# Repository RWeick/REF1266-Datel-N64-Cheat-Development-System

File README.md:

# REF1266-Datel-N64-Cheat-Development-System
Everything necessary to produce the Datel N64 Cheat Development System

This device is explained in some detail [here](https://www.nesworld.com/n64-dateltrainercart.php).

Brought back from the edge of extinction, this is the predecessor to the N64 Gameshark Pro's Code Generator. This device is used to hack codes for the N64 in concert with the [Datel PC Comms ISA Card](https://github.com/RWeick/REF1190-Datel-PC-Comms-Link-ISA-Card). The firmwares listed show the compatible games it can hack codes for. I have not yet tested if they are compatible with other games as well. The firmware can be flashed to the device by writing it directly to the eeproms prior to soldering them down or via the Sanni Cartridge Reader's Flash Gameshark function. Once a firmware is written, the firmwares can be swapped using the Sharklink software in the PC Comms Link repository.

As I have not ever seen one of these myself in person, the dimensions of the PCB may be slightly off from the original. However, the schematic and pcb trace connections are 100% the same as the original as verified by testing the device. This was possible due to the extensive reverse engineering I've already done on the N64 Gameshark. All necessary parts can be harvested from any N64 Gameshark or Gameshark Pro, with the exception of the parallel port which is a horizontal mounted male port. Happy making.

PCB Thickness: 1.2 mm

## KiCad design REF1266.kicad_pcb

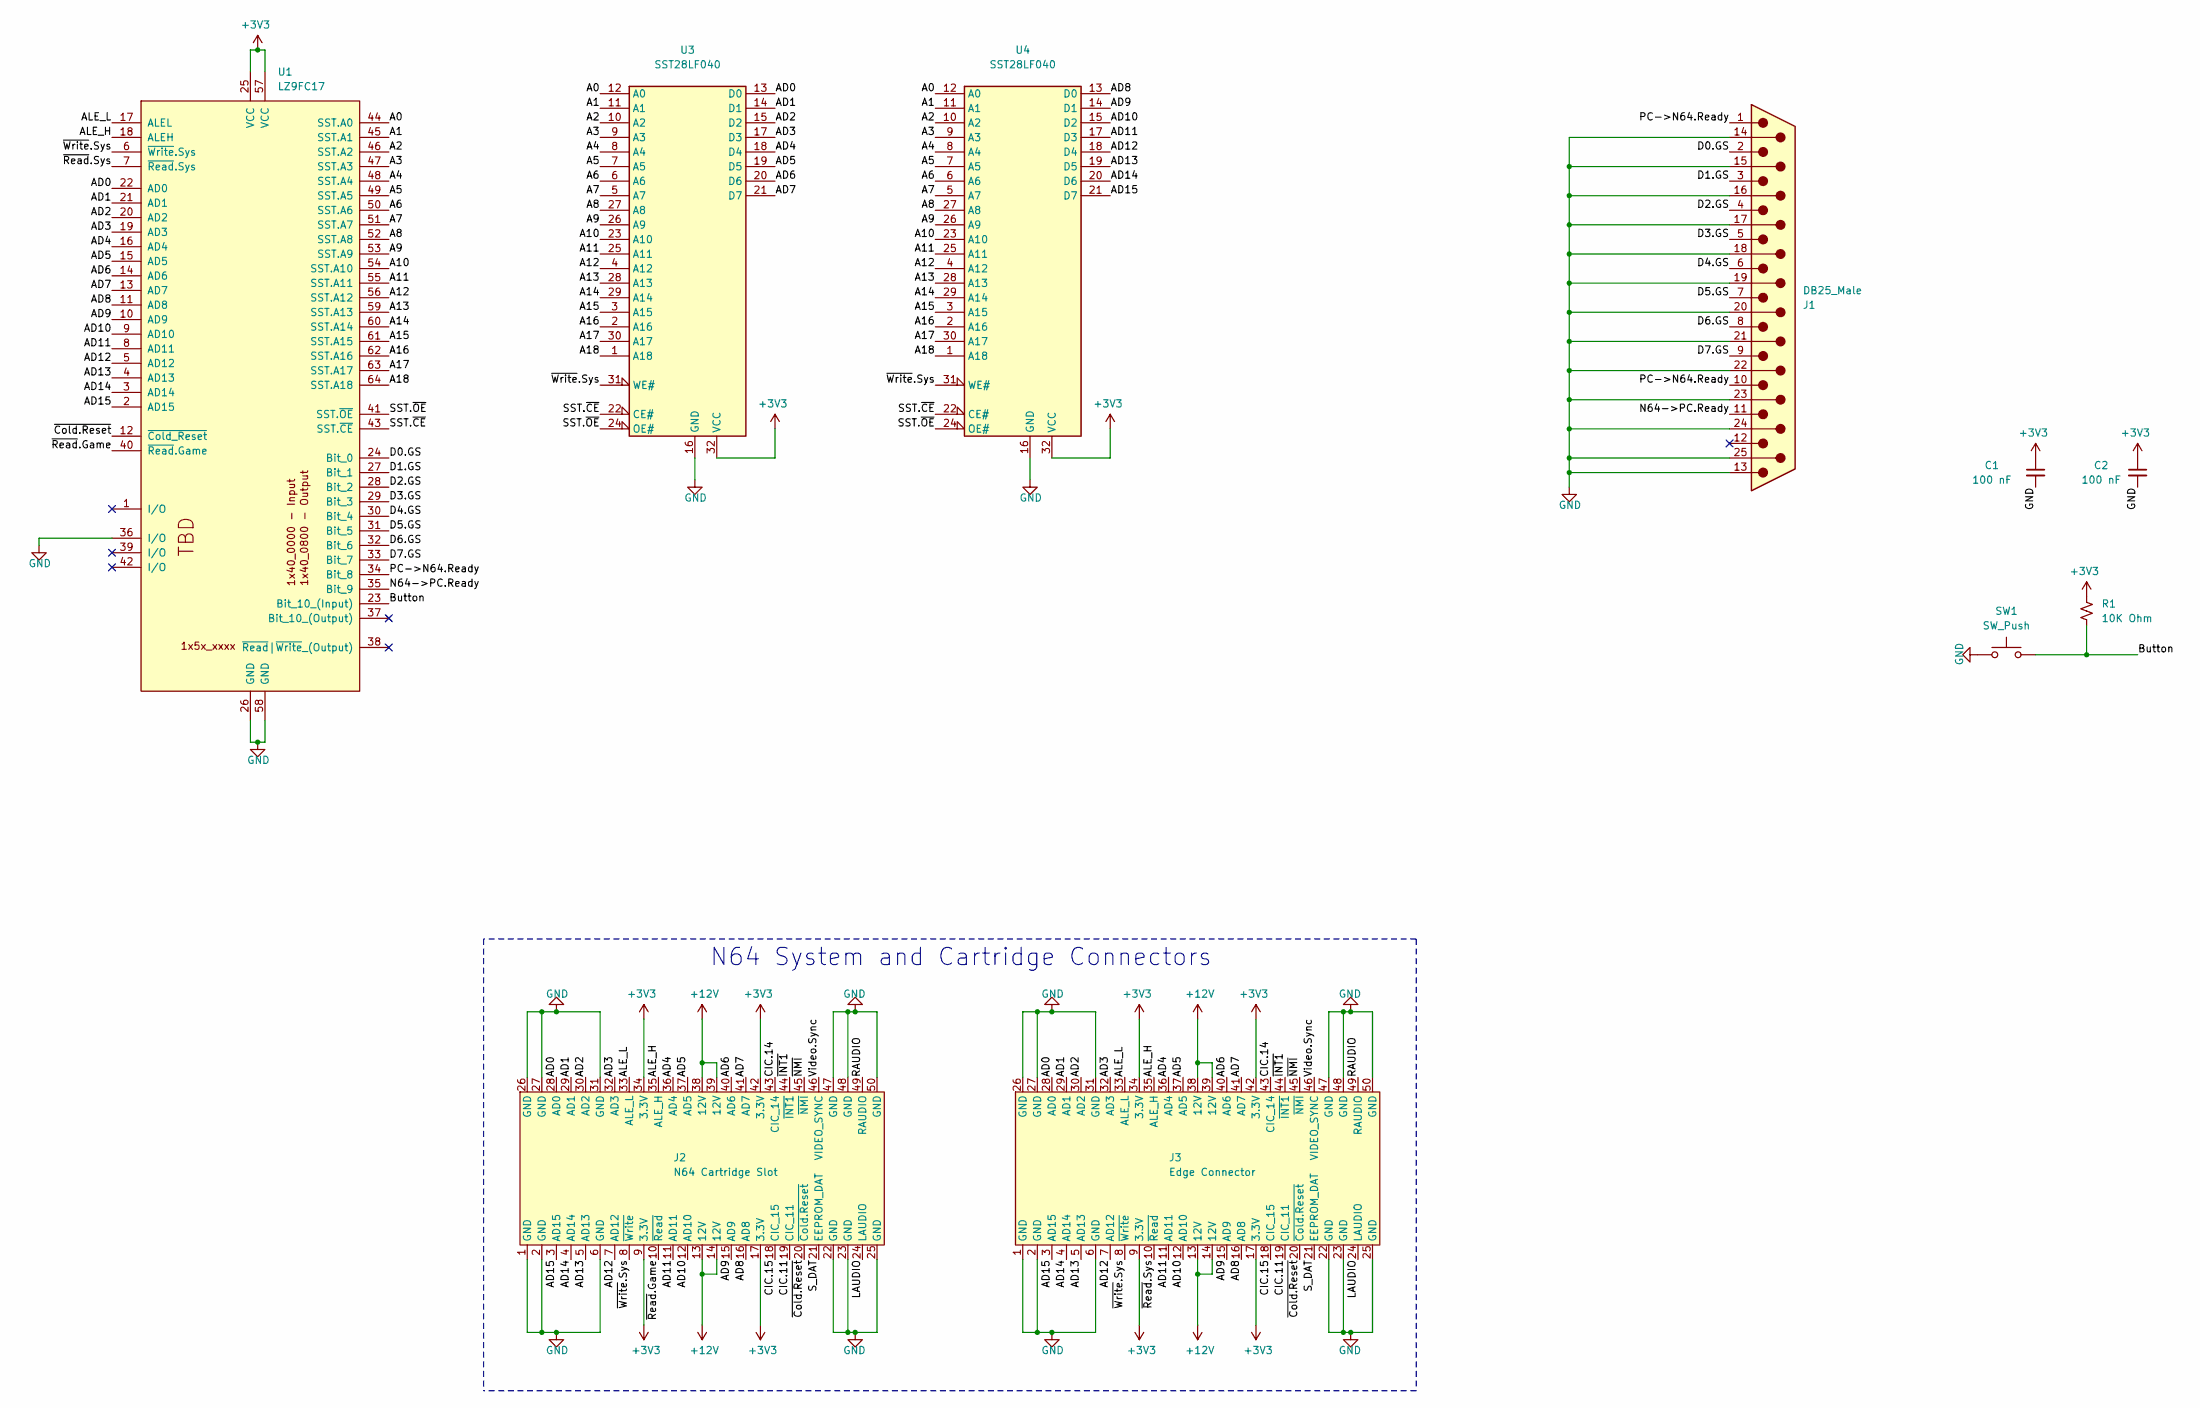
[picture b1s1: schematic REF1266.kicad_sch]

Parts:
C1, C2: 100 nF; 100 nF Cap
J1: DB25_Male; DSUB-25_Socket_Vertical_P2.77x2.84mm_MountingHoles
J2: N64 Cartridge Slot; Cartridge Slot
J3: Edge Connector; Bottom Edge Connector
R1: 10K Ohm; 10k Ohm Resistor
SW1: SW_Push; 6mm Push Button
U1: LZ9FC17; LZ9FC17 GAL
U3, U4: SST28LF040; PLCC32

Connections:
+3V3: C1.1, C2.1, J2.9 (3.3V), J2.17 (3.3V), J2.34 (3.3V), J2.42 (3.3V), J3.9 (3.3V), J3.17 (3.3V), J3.34 (3.3V), J3.42 (3.3V), R1.2, U1.25 (VCC), U1.57 (VCC), U3.32 (VCC), U4.32 (VCC)
+12V: J2.13 (12V), J2.14 (12V), J2.38 (12V), J2.39 (12V), J3.13 (12V), J3.14 (12V), J3.38 (12V), J3.39 (12V)
/A0: U1.44 (SST.A0), U3.12 (A0), U4.12 (A0)
/A1: U1.45 (SST.A1), U3.11 (A1), U4.11 (A1)
/A2: U1.46 (SST.A2), U3.10 (A2), U4.10 (A2)
/A3: U1.47 (SST.A3), U3.9 (A3), U4.9 (A3)
/A4: U1.48 (SST.A4), U3.8 (A4), U4.8 (A4)
/A5: U1.49 (SST.A5), U3.7 (A5), U4.7 (A5)
/A6: U1.50 (SST.A6), U3.6 (A6), U4.6 (A6)
/A7: U1.51 (SST.A7), U3.5 (A7), U4.5 (A7)
/A8: U1.52 (SST.A8), U3.27 (A8), U4.27 (A8)
/A9: U1.53 (SST.A9), U3.26 (A9), U4.26 (A9)
/A10: U1.54 (SST.A10), U3.23 (A10), U4.23 (A10)
/A11: U1.55 (SST.A11), U3.25 (A11), U4.25 (A11)
/A12: U1.56 (SST.A12), U3.4 (A12), U4.4 (A12)
/A13: U1.59 (SST.A13), U3.28 (A13), U4.28 (A13)
/A14: U1.60 (SST.A14), U3.29 (A14), U4.29 (A14)
/A15: U1.61 (SST.A15), U3.3 (A15), U4.3 (A15)
/A16: U1.62 (SST.A16), U3.2 (A16), U4.2 (A16)
/A17: U1.63 (SST.A17), U3.30 (A17), U4.30 (A17)
/A18: U1.64 (SST.A18), U3.1 (A18), U4.1 (A18)
/AD0: J2.28 (AD0), J3.28 (AD0), U1.22 (AD0), U3.13 (D0)
/AD1: J2.29 (AD1), J3.29 (AD1), U1.21 (AD1), U3.14 (D1)
/AD2: J2.30 (AD2), J3.30 (AD2), U1.20 (AD2), U3.15 (D2)
/AD3: J2.32 (AD3), J3.32 (AD3), U1.19 (AD3), U3.17 (D3)
/AD4: J2.36 (AD4), J3.36 (AD4), U1.16 (AD4), U3.18 (D4)
/AD5: J2.37 (AD5), J3.37 (AD5), U1.15 (AD5), U3.19 (D5)
/AD6: J2.40 (AD6), J3.40 (AD6), U1.14 (AD6), U3.20 (D6)
/AD7: J2.41 (AD7), J3.41 (AD7), U1.13 (AD7), U3.21 (D7)
/AD8: J2.16 (AD8), J3.16 (AD8), U1.11 (AD8), U4.13 (D0)
/AD9: J2.15 (AD9), J3.15 (AD9), U1.10 (AD9), U4.14 (D1)
/AD10: J2.12 (AD10), J3.12 (AD10), U1.9 (AD10), U4.15 (D2)
/AD11: J2.11 (AD11), J3.11 (AD11), U1.8 (AD11), U4.17 (D3)
/AD12: J2.7 (AD12), J3.7 (AD12), U1.5 (AD12), U4.18 (D4)
/AD13: J2.5 (AD13), J3.5 (AD13), U1.4 (AD13), U4.19 (D5)
/AD14: J2.4 (AD14), J3.4 (AD14), U1.3 (AD14), U4.20 (D6)
/AD15: J2.3 (AD15), J3.3 (AD15), U1.2 (AD15), U4.21 (D7)
/ALE_H: J2.35 (ALE_H), J3.35 (ALE_H), U1.18 (ALEH)
/ALE_L: J2.33 (ALE_L), J3.33 (ALE_L), U1.17 (ALEL)
/Button: R1.1, SW1.2, U1.23 (Bit_10_(Input))
/CIC.11: J2.19 (CIC_11), J3.19 (CIC_11)
/CIC.14: J2.43 (CIC_14), J3.43 (CIC_14)
/CIC.15: J2.18 (CIC_15), J3.18 (CIC_15)
/D0.GS: J1.2, U1.24 (Bit_0)
/D1.GS: J1.3, U1.27 (Bit_1)
/D2.GS: J1.4, U1.28 (Bit_2)
/D3.GS: J1.5, U1.29 (Bit_3)
/D4.GS: J1.6, U1.30 (Bit_4)
/D5.GS: J1.7, U1.31 (Bit_5)
/D6.GS: J1.8, U1.32 (Bit_6)
/D7.GS: J1.9, U1.33 (Bit_7)
/LAUDIO: J2.24 (LAUDIO), J3.24 (LAUDIO)
/N64->PC.Ready: J1.11, U1.35 (Bit_9)
/PC->N64.Ready: J1.1, J1.10, U1.34 (Bit_8)
/RAUDIO: J2.49 (RAUDIO), J3.49 (RAUDIO)
/SST.~CE: U1.43 (SST.~CE), U3.22 (CE#), U4.22 (CE#)
/SST.~OE: U1.41 (SST.~OE), U3.24 (OE#), U4.24 (OE#)
/S_DAT: J2.21 (EEPROM_DAT), J3.21 (EEPROM_DAT)
/Video.Sync: J2.46 (VIDEO_SYNC), J3.46 (VIDEO_SYNC)
/~Cold.Reset: J2.20 (~Cold.Reset), J3.20 (~Cold.Reset), U1.12 (~Cold_Reset)
/~INT1: J2.44 (~INT1), J3.44 (~INT1)
/~NMI: J2.45 (~NMI), J3.45 (~NMI)
/~Read.Game: J2.10 (~Read), U1.40 (~Read.Game)
/~Read.Sys: J3.10 (~Read), U1.7 (~Read.Sys)
/~Write.Sys: J2.8 (~Write), J3.8 (~Write), U1.6 (~Write.Sys), U3.31 (WE#), U4.31 (WE#)
GND: C1.2, C2.2, J1.13, J1.14, J1.15, J1.16, J1.17, J1.18, J1.19, J1.20, J1.21, J1.22, J1.23, J1.24, J1.25, J2.1 (GND), J2.2 (GND), J2.6 (GND), J2.22 (GND), J2.23 (GND), J2.25 (GND), J2.26 (GND), J2.27 (GND), J2.31 (GND), J2.47 (GND), J2.48 (GND), J2.50 (GND), J3.1 (GND), J3.2 (GND), J3.6 (GND), J3.22 (GND), J3.23 (GND), J3.25 (GND), J3.26 (GND), J3.27 (GND), J3.31 (GND), J3.47 (GND), J3.48 (GND), J3.50 (GND), SW1.1, U1.26 (GND), U1.36 (I/O), U1.58 (GND), U3.16 (GND), U4.16 (GND)

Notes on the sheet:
N64 System and Cartridge Connectors

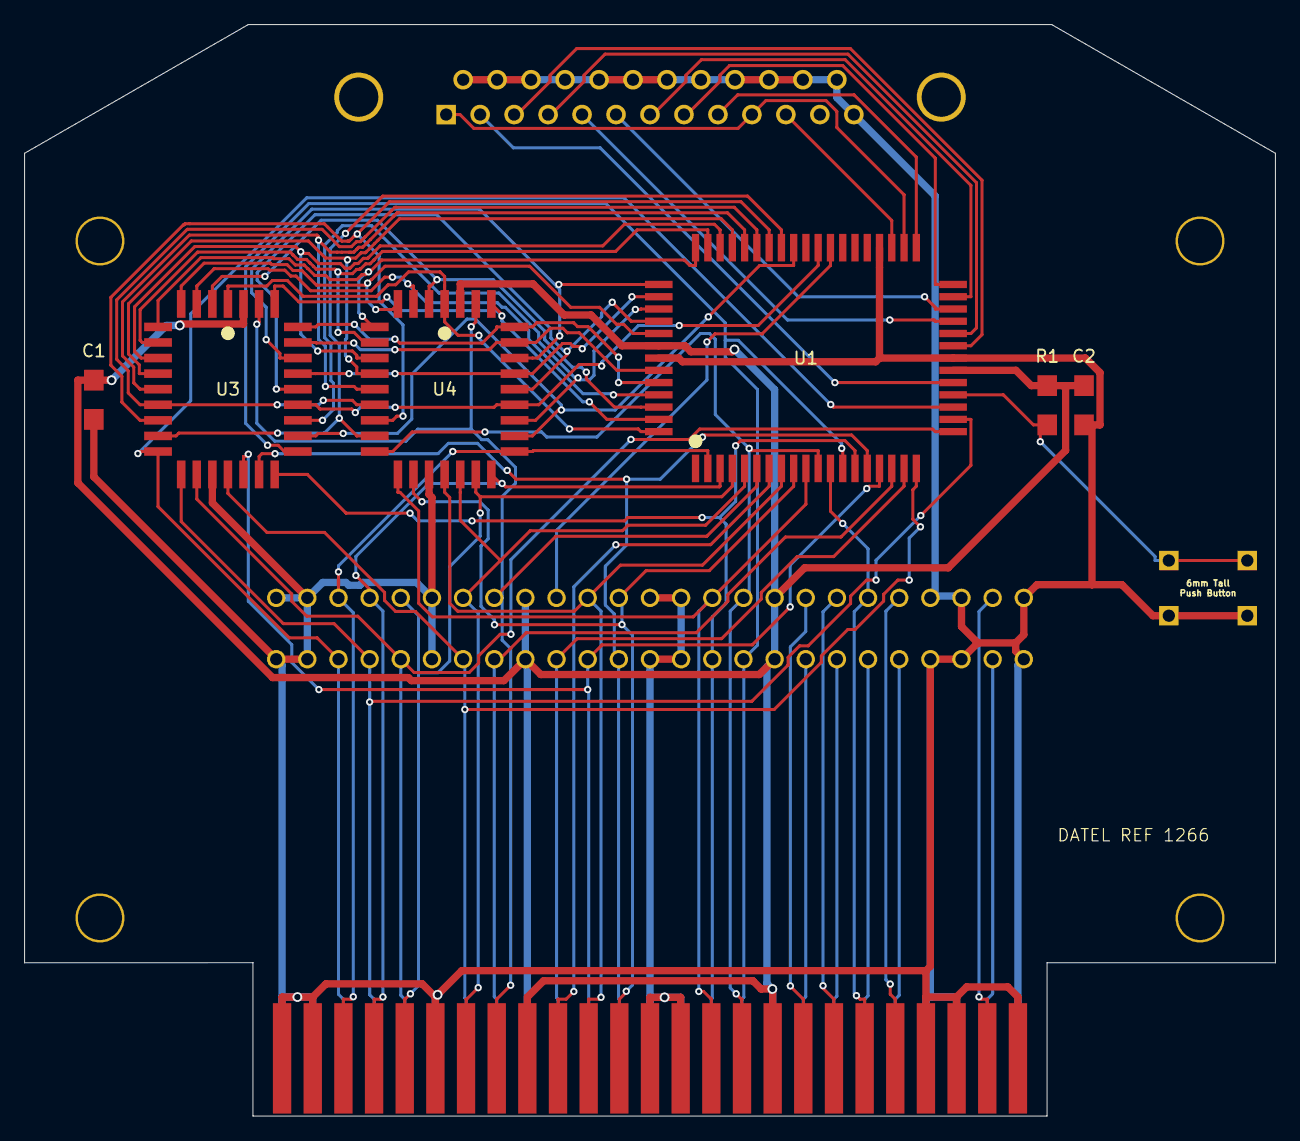
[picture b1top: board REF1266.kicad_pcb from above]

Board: 2 copper layers, 102.0 x 89.0 mm, 11 parts (0 on the bottom side), 66 nets.

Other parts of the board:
Holes: Drill Holes
